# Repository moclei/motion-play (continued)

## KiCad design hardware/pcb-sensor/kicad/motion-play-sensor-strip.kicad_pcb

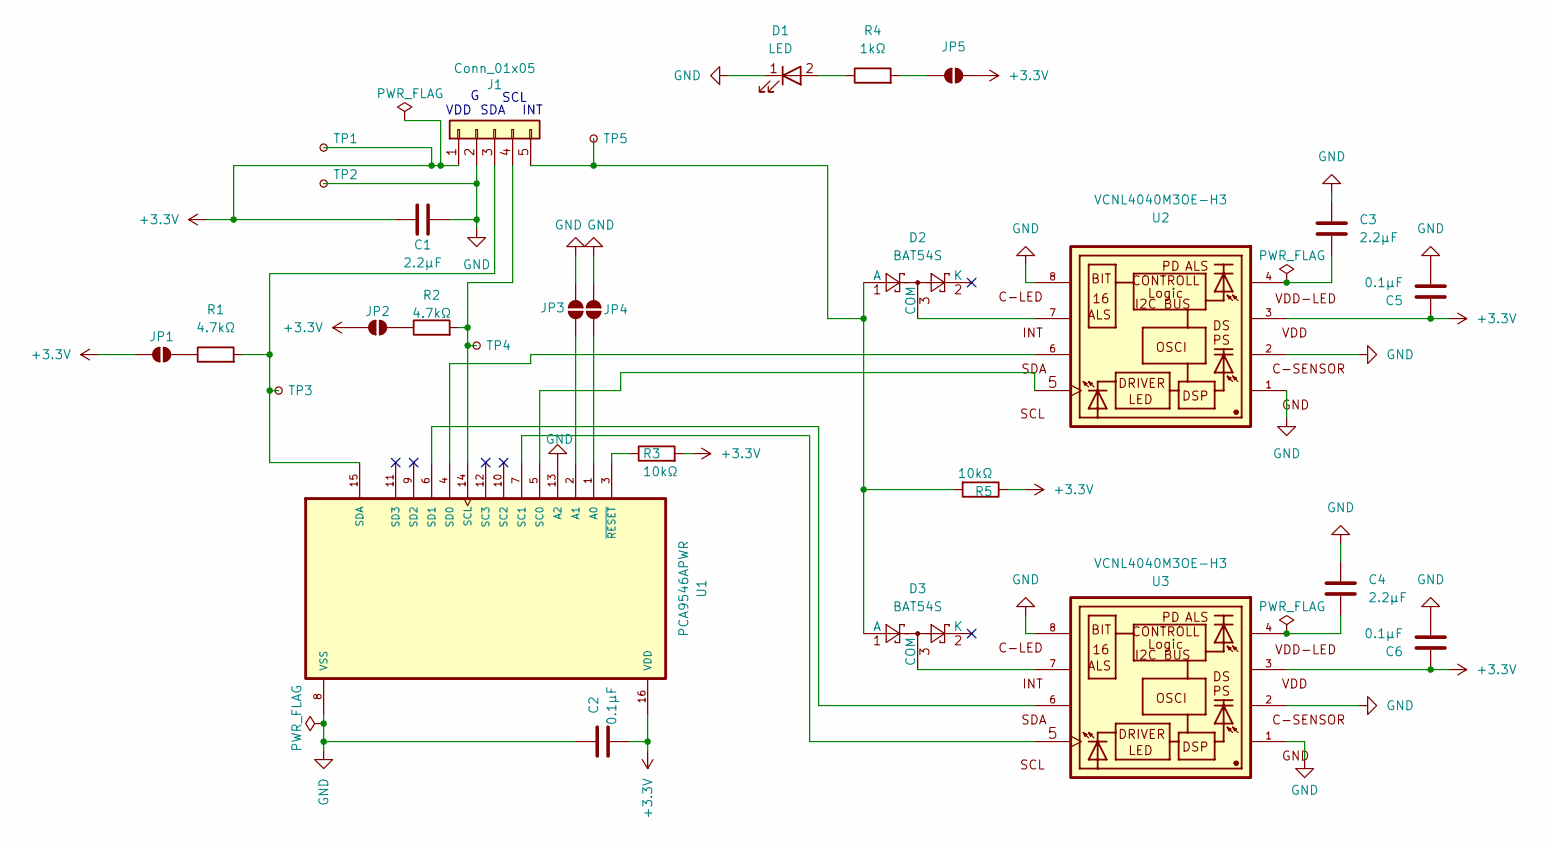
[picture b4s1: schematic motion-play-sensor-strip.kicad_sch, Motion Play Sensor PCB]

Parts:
C1, C3, C4: 2.2µF; C_0603_1608Metric; LCSC Part C23630
C2, C5, C6: 0.1µF; C_0603_1608Metric; LCSC Part C14663
D1: LED; LED_0603_1608Metric; LCSC Part C19171301
D2, D3: BAT54S; SOT-23; LCSC Part C727126
J1: Conn_01x05; JST_SH_SM05B-SRSS-TB_1x05-1MP_P1.00mm_Horizontal; LCSC Part C136657
JP1, JP2, JP3, JP4, JP5: SolderJumper_2_Open; SolderJumper-2_P1.3mm_Open_RoundedPad1.0x1.5mm
R1, R2: 4.7kΩ; R_0603_1608Metric; LCSC Part C99782
R3, R5: 10kΩ; R_0603_1608Metric; LCSC Part C25804
R4: 1kΩ; R_0603_1608Metric; LCSC Part C22548
TP1, TP2, TP3, TP4, TP5: TestPoint_Small; TestPoint_Pad_D1.5mm
U1: PCA9546APWR; SOP65P640X120-16N; LCSC Part C400705
U2, U3: VCNL4040M3OE-H3; VISHAY_VCNL4040; LCSC Part C142526

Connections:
+3.3V: C1.2, C2.2, C5.1, C6.1, J1.1, JP1.1 (A), JP2.1 (A), JP5.2 (B), R3.2, R5.1, TP1.1, U1.16 (VDD), U2.3, U3.3
GND: C1.1, C2.1, C3.1, C4.1, C5.2, C6.2, D1.1 (K), J1.2, JP3.2 (B), JP4.2 (B), TP2.1, U1.8 (VSS), U1.13 (A2), U2.1, U2.2, U2.8, U3.1, U3.2, U3.8
unnamed: C3.2, U2.4
unnamed: C4.2, U3.4
unnamed: D1.2 (A), R4.1
unnamed: D2.1 (A), D3.1 (A), J1.5, R5.2, TP5.1
unnamed: D2.3 (COM), U2.7
unnamed: D3.3 (COM), U3.7
unnamed: J1.3, R1.2, TP3.1, U1.15 (SDA)
unnamed: J1.4, R2.2, TP4.1, U1.14 (SCL)
unnamed: JP1.2 (B), R1.1
unnamed: JP2.2 (B), R2.1
unnamed: JP3.1 (A), U1.2 (A1)
unnamed: JP4.1 (A), U1.1 (A0)
unnamed: JP5.1 (A), R4.2
unnamed: U1.5 (SC0), U2.5
unnamed: U1.7 (SC1), U3.5
unnamed: U1.4 (SD0), U2.6
unnamed: U1.6 (SD1), U3.6
unnamed: R3.1, U1.3 (~RESET)

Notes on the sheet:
SDA
SCL
VDD
INT

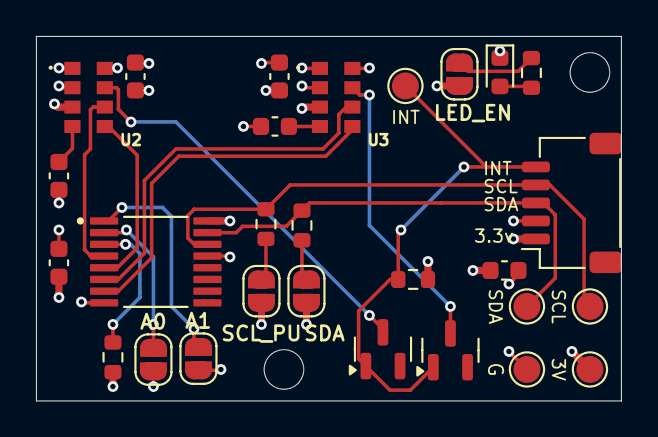
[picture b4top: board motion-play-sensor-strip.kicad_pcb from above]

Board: 4 copper layers, 32.5 x 20.2 mm, 28 parts (0 on the bottom side), 20 nets.

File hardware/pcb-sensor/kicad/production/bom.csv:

Designator,Footprint,Quantity,Value,LCSC Part #
"C1, C3, C4",0603,3,2.2µF,C23630
"C2, C5, C6",0603,3,0.1µF,C14663
D1,0603,1,LED,C19171301
"D2, D3",SOT-23,2,BAT54S,C727126
J1,JST_SH_SM05B-SRSS-TB_1x05-1MP_P1.00mm_Horizontal,1,Conn_01x05,C136657
"R1, R2",0603,2,4.7kΩ,C99782
"R3, R5",0603,2,10kΩ,C25804
R4,0603,1,1kΩ,C22548
"TP1, TP2, TP3, TP4, TP5",TestPoint_Pad_D1.5mm,5,TestPoint_Small,
U1,SOP65P640X120-16N,1,PCA9546APWR,C400705
"U2, U3",VISHAY_VCNL4040,2,VCNL4040M3OE-H3,C142526

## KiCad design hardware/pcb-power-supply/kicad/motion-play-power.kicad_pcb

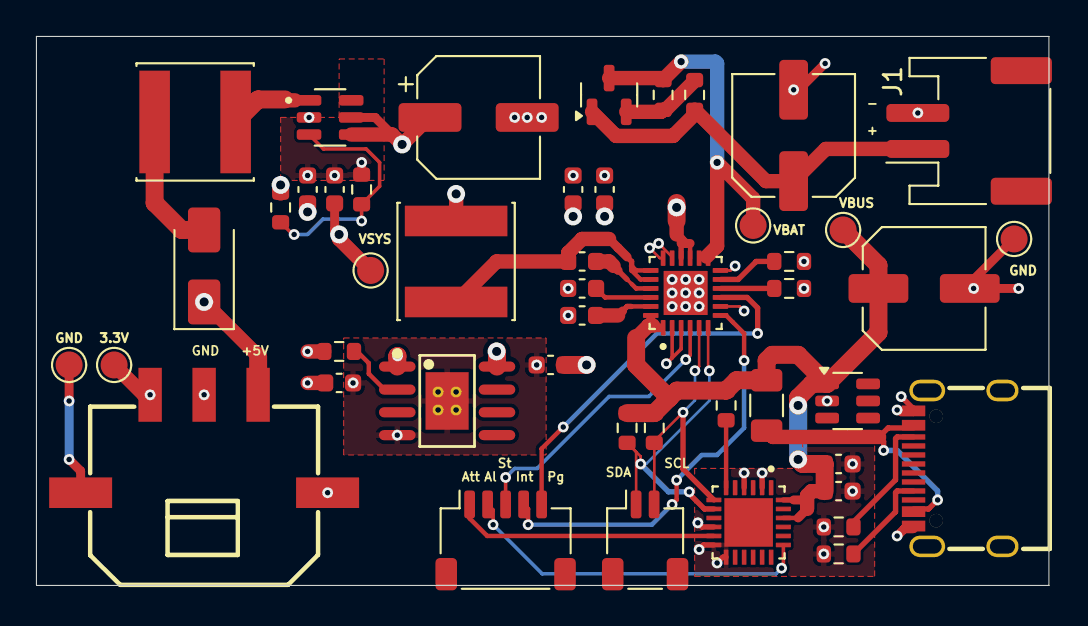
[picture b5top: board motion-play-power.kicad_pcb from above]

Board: 4 copper layers, 56.2 x 30.5 mm, 47 parts (0 on the bottom side), 29 nets.

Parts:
3.3V: +3.3V TP; TestPoint_Pad_D1.5mm
C1: 0.1µF; C_0603_1608Metric
C2: 4.7µF; C_0603_1608Metric
C3: 100nF; C_0603_1608Metric
C4, C6, C7: 10uF; C_0603_1608Metric
C5: 4.7uF; C_0603_1608Metric
C8: 220µF; CP_Elec_6.3x7.7
C9, C10: 22µF; C_0603_1608Metric
C11, C12: 2.2uF; C_0603_1608Metric
C13, C14: C_Polarized_Small_US; C_Elec_6.3x5.4
CN1: X3025WRS-03D-LPSW; CONN-SMD_3P-H-P3.00-R_X3025WRS-03D-LPSW
D1: 40V Independent Type 550mV@5A 5A SMA(DO-214AC) Sc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; D_SMA
F1: Fuse; Fuse_1206_3216Metric
GND: GND TP; TestPoint_Pad_D1.5mm
GND#2: GND PD TP; TestPoint_Pad_D1.5mm
J1: Conn_01x02; JST_PH_S2B-PH-SM4-TB_1x02-1MP_P2.00mm_Horizontal
J3: Conn_01x02; JST_SH_SM02B-SRSS-TB_1x02-1MP_P1.00mm_Horizontal
J4: Conn_01x05; JST_SH_SM05B-SRSS-TB_1x05-1MP_P1.00mm_Horizontal
L1: 2.2uH; L_Changjiang_FNR6028S
L2: 4.7uH; L_Changjiang_FNR6028S
Q1: PMOS; SOT-23
R1, R2: 5.1kΩ; R_0603_1608Metric
R3, R4, R5, R9, R11: 10kΩ; R_0603_1608Metric
R6: 2.7k; R_0603_1608Metric
R7, R8: 100k; R_0603_1608Metric
R10: 47kΩ; R_0603_1608Metric
TH1: Thermistor_NTC; R_0603_1608Metric
TP3: VBUS TP; TestPoint_Pad_D1.5mm
U1: STUSB4500LQTR; QFN50P400X400X100-25N
U2: USBLC6-2SC6; SOT-23-6
U3: BQ24195RGET; QFN50P400X400X100-25N
U4: MT3608; SOT95P280X145-6N
U5: LR1801G-33-SH2-R; HSOP-8_L5.0-W4.0-P1.27-LS6.2-BL-EP
USBC1: TYPE-C-31-M-12; USB-C_SMD-TYPE-C-31-M-12
VBAT: VBAT TP; TestPoint_Pad_D1.5mm
VSYS: VSYS TP; TestPoint_Pad_D1.5mm

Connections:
+3.3V: 3.3V.1, C12.1, CN1.3, R11.2, U5.1 (VOUT)
+5V: C10.1, CN1.1, D1.1 (K), R10.2
/Battery Management/CHRG_INT: J4.4, U3.7 (INT)
/Battery Management/CHRG_PG: J4.5, U3.9 (CE)
/Battery Management/CHRG_STAT: J4.3, U3.4 (STAT)
/Battery Management/VSYS: C6.2, C7.2, C8.1, C9.1, C11.1, L1.2, U3.15 (SYS1), U3.16 (SYS2), U4.4 (EN), U4.5 (IN), U5.8 (VIN), VSYS.1
/Connectors/USB_ALERT: J4.2, U1.19 (ALERT)
/Connectors/USB_ATTACH: J4.1, U1.11 (ATTACH)
GND: C1.2, C2.2, C4.2, C5.2, C6.1, C7.1, C8.2, C9.2, C10.2, C11.2, C12.2, C13.2, C14.2, CN1.2, CN1.4, CN1.5, GND.1, GND#2.1, J1.2, R1.2, R2.2, R6.1, R9.1, TH1.1, U1.2 (CC1), U1.4 (CC2), U1.10 (GND), U1.12 (ADDR0), U1.13 (ADDR1), U1.25 (EXP), U2.2 (GND), U3.2 (D+), U3.3 (D-), U3.8 (OTG), U3.12 (TS2), U3.17 (PGND1), U3.18 (PGND2), U3.25 (GND), U4.2 (GND), U5.4 (GND), U5.9 (EP), USBC1.0 (SH), USBC1.A1 (GND), USBC1.A12 (GND), USBC1.B1 (GND), USBC1.B12 (GND)
I2C_SCL: J3.2, R4.1, U1.7 (SCL), U3.5 (SCL)
I2C_SDA: J3.1, R3.1, U1.8 (SDA), U3.6 (SDA)
unnamed: D1.2 (A), L2.2
unnamed: F1.1, USBC1.A4 (VBUS), USBC1.A9 (VBUS), USBC1.B4 (VBUS), USBC1.B9 (VBUS)
unnamed: C13.1, J1.1, Q1.1 (D), R8.2
unnamed: Q1.2 (G), R7.2, R8.1
unnamed: R5.1, U1.6 (RESET)
unnamed: C3.1, U3.21 (BTST)
unnamed: R6.2, U3.10 (ILIM)
unnamed: C4.1, U3.23 (PMID)
unnamed: C5.1, U3.22 (REGN)
unnamed: C3.2, L1.1, U3.19 (SW1), U3.20 (SW2)
unnamed: TH1.2, U3.11 (TS1)
unnamed: R9.2, R10.1, U4.3 (FB)
unnamed: L2.1, U4.1 (SW)
unnamed: R11.1, U5.2 (ON/~OFF)
unnamed: R1.1, USBC1.A5 (CC1)
unnamed: R2.1, USBC1.B5 (CC2)
Protected_VBUS: C1.1, C2.1, C14.1, F1.2, R3.2, R4.2, R5.2, TP3.1, U1.22 (VSYS), U1.24 (VDD), U2.1 (I/O1), U3.1 (VBUS1), U3.24 (VBUS2)
VBAT: Q1.3 (S), R7.1, U3.13 (BAT1), U3.14 (BAT2), VBAT.1

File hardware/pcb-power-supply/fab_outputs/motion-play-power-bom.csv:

Comment,Designator,Footprint,LCSC Part Number
100nF Unpolarized capacitor,"C1, C3",C_0603_1608Metric,C14663
10µF Unpolarized capacitor,"C4,C6,C7",C_0603_1608Metric,C96446
4.7µF Unpolarized capacitor,"C2, C5",C_0603_1608Metric,C19666
220µF Unpolarized capacitor,C8,CP_Elec_6.3x7.7,C3342
22µF Unpolarized capacitor,"C9,C10",C_0603_1608Metric,C59461
2.2µF Unpolarized capacitor,"C11,C12",C_0603_1608Metric,C23630
47µF Polarized Capacitor,"C13,C14",C_Elec_6.3x5.4,C2836440
"40V Independent Type 550mV@5A 5A SMA(DO-214AC) Schottky Diodes ROHS Diode, small symbol",D1,D_SMA,C22452
Fuse Fuse,F1,Fuse_1206_3216Metric,C2897466
X3025WRS-03D-LPSW,CN1,CONN-SMD_3P-H-P3.00-R_X3025WRS-03D-LPSW,C405941
PH 2mm 2-pin connector horizontal,J1,JST_PH_S2B-PH-SM4-TB_1x02-1MP_P2.00mm_Horizontal,C18221575
SH 1mm 2-pin connector horizontal,J3,JST_SH_SM02B-SRSS-TB_1x02-1MP_P1.00mm_Horizontal,C160402
SH 1mm 5-pin connector horizontal,J4,JST_SH_SM05B-SRSS-TB_1x05-1MP_P1.00mm_Horizontal,C136657
2.2uH Inductor,L1,L_Changjiang_FNR6028S,C266426
4.7uH Inductor,L2,L_Changjiang_FNR6028S,C307880
"PMOS P-MOSFET transistor, drain/source/gate",Q1,SOT-23,C3040193
5.1kΩ Resistor,"R1,R2",R_0603_1608Metric,C23186
10kΩ Resistor,"R3,R4,R5,R9,R11",R_0603_1608Metric,C25804
2.7k Resistor,R6,R_0603_1608Metric,C13167
100kΩ Resistor,"R7,R8",R_0603_1608Metric,C14675
47kΩ Resistor,R10,R_0603_1608Metric,C25819
"Thermistor_NTC Temperature dependent resistor, negative temperature coefficient",TH1,R_0603_1608Metric,C13564
STUSB4500LQTR,U1,QFN50P400X400X100-25N,C506650
"USBLC6-2SC6 Very low capacitance ESD protection diode, 2 data-line, SOT-23-6",U2,SOT-23-6,C7519
BQ24195RGET,U3,QFN50P400X400X100-25N,C2876710
MT3608,U4,SOT95P280X145-6N,C84817
LR1801G-33-SH2-R,U5,HSOP-8_L5.0-W4.0-P1.27-LS6.2-BL-EP,C410479
TYPE-C-31-M-12,USBC1,USB-C_SMD-TYPE-C-31-M-12,C165948

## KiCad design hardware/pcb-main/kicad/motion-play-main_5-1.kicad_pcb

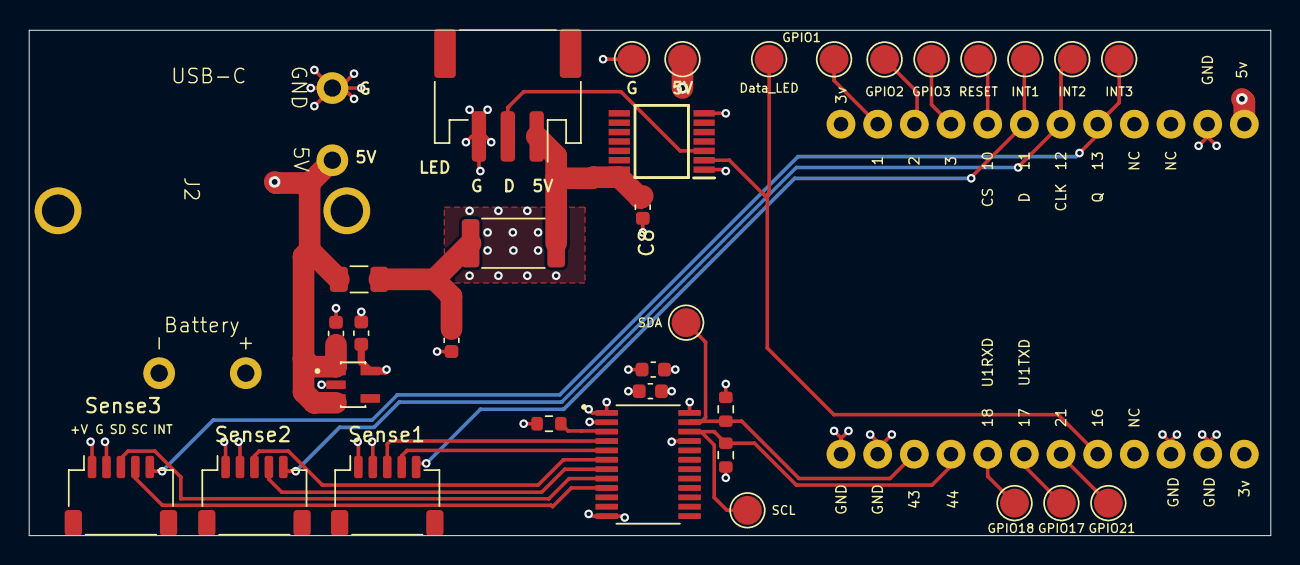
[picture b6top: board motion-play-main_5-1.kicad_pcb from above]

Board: 4 copper layers, 86.0 x 35.0 mm, 35 parts (0 on the bottom side), 25 nets.

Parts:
C1: 1µF; C_0603_1608Metric
C2: 2.2µF; C_0603_1608Metric
C7, C9: 100nF; C_0603_1608Metric
C8, C10: 10uF; C_0603_1608Metric
F1: 3A; Fuse_1206_3216Metric
IC1: SN74AHCT125PWR; SOP65P640X120-14N
J2: DWEII Power Module; USBC_Power_Module
J3: LED_Strip; JST_PH_S3B-PH-SM4-TB_1x03-1MP_P2.00mm_Horizontal
J4, J5, J6: Conn_01x05; JST_SH_SM05B-SRSS-TB_1x05-1MP_P1.00mm_Horizontal
R6: 10kΩ; R_0603_1608Metric
R27: 0.1R; R_2512_6332Metric
R28, R29: 2.2kΩ; R_0603_1608Metric
TPIO1, TPIO2, TPIO3, TPIO10, TPIO11, TPIO12, TPIO13, TPIO16, TPIO17, TPIO18, TPIO21, TPIO43, TPIO44: TestPoint; TestPoint_Pad_D2.0mm
TP_5V1: TestPoint; TestPoint_Pad_D2.0mm
TP_GND1: TestPoint; TestPoint_Pad_D2.0mm
U1: AP2112K-3.3TRG1; SOT95P285X140-5N
U2: T-Display-S3
U4: TCA9548APWR; SOP65P640X120-24N

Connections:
+3.3V: C2.2, C9.2, C10.2, J4.1, J5.1, J6.1, R6.2, R28.2, R29.2, U1.5 (VOUT), U4.24 (VCC)
+5V: C1.2, F1.1, J2.2 (5V), TP_5V1.1, U1.1 (VIN), U1.3 (EN), U2.12 (5V)
/I2C_SCL: R29.1, TPIO44.1, U2.16 (44), U4.22 (SCL)
/I2C_SDA: R28.1, TPIO43.1, U2.15 (43), U4.23 (SDA)
/INT1: J4.5, TPIO11.1, U2.6 (11)
/INT2: J5.5, TPIO12.1, U2.7 (12)
/INT3: J6.5, TPIO13.1, U2.8 (13)
/LED Controller/+5V_TO_LEDS: C8.2, IC1.14 (VCC), J3.1, R27.2
/LED Controller/DATA_IN: IC1.2 (1A), TPIO16.1, U2.20 (16)
/LED Controller/DATA_TO_LEDS: IC1.3 (1Y), J3.2
/TCA9548A_Subsystem/CH0_SCL: J4.4, U4.5 (SC0)
/TCA9548A_Subsystem/CH0_SDA: J4.3, U4.4 (SD0)
/TCA9548A_Subsystem/CH1_SCL: J5.4, U4.7 (SC1)
/TCA9548A_Subsystem/CH1_SDA: J5.3, U4.6 (SD1)
/TCA9548A_Subsystem/CH2_SCL: J6.4, U4.9 (SC2)
/TCA9548A_Subsystem/CH2_SDA: J6.3, U4.8 (SD2)
/TCA9548A_Subsystem/TCA_RESET: R6.1, TPIO10.1, U2.5 (10), U4.3 (~RESET)
GND: C1.1, C2.1, C7.1, C8.1, C9.1, C10.1, IC1.1 (1~OE), IC1.7 (GND), J2.1 (GND), J3.3, J4.2, J5.2, J6.2, TP_GND1.1, U1.2 (GND), U2.11 (GND), U2.13 (GND), U2.14 (GND), U2.22 (GND), U2.23 (GND), U4.1 (A0), U4.2 (A1), U4.12 (GND), U4.21 (A2)
unnamed: C7.2, F1.2, R27.1
unnamed: TPIO1.1, U2.2 (1)
unnamed: TPIO2.1, U2.3 (2)
unnamed: TPIO3.1, U2.4 (3)
unnamed: TPIO17.1, U2.18 (17)
unnamed: TPIO18.1, U2.17 (18)
unnamed: TPIO21.1, U2.19 (21)

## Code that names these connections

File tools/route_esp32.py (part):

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      R51 p1 (139.8, 130.1) → +3.3V via (In2.Cu zone covers this area)
      SW3 p2 (137.6, 130.5) → GND via
    """
    n_boot = nets['/ESP32_S3/GPIO0_BOOT']
    n33 = nets['+3.3V']
    ngnd = nets['GND']

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
def route_priority4_i2c(board, nets, log):
    """
    I2C_SDA: extend from U4 pin 23 (149.07, 116.92) to U3 pin 37 (139.9, 112.7)
    I2C_SCL: extend from U4 pin 22 (149.07, 116.27) to U3 pin 36 (139.9, 113.9)

    Both route on F.Cu: west from U4 area, then diagonal to U3 right side.
    """
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
def route_priority4_tca_reset(board, nets, log):
    """
    TCA_RESET: extend from existing B.Cu dead end (153.31, 113.37) to U3 pin 18 (128.0, 126.7).

    Route on B.Cu: diagonal southwest from existing endpoint to near U3 pin 18,
    then via to F.Cu for the final connection.
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
def route_priority4_led_data(board, nets, log):
    """
    LED_DATA: U3 pin 9 (122.4, 119.0) → IC1 pin 2 area (144.46, 134.20).

    Route via B.Cu to avoid F.Cu congestion:
    F.Cu short → via → B.Cu diagonal → via → F.Cu to IC1.
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
def route_priority4_chrg_int(board, nets, log):
    """
    CHRG_INT: U3 pin 23 (134.4, 126.7) → existing routing near R38 area.

    Existing CHRG_INT has a dead end at (98.94, 118.81) on F.Cu.
    Route via B.Cu: U3 p23 → via → B.Cu west → via → F.Cu to join existing trace.
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    nets = build_net_map(board)

    # Verify required nets exist
    required = ['+5V', 'GND', '+3.3V', '/ESP32_S3/EN', '/ESP32_S3/GPIO0_BOOT',
                '/I2C_SDA', '/I2C_SCL', '/TCA_RESET', '/LED_DATA', '/CHRG_INT']
    missing = [n for n in required if n not in nets]
    if missing:
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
